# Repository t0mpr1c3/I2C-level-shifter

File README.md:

I2C-level-shifter
=================

I2C voltage level converter with LDO voltage regulator.

Following NXP application note AN10441.

Released under the [Creative Commons License Attribution-ShareAlike 3.0](http://creativecommons.org/licenses/by-sa/3.0/)

Version history
---------------

_IL01_

First version.

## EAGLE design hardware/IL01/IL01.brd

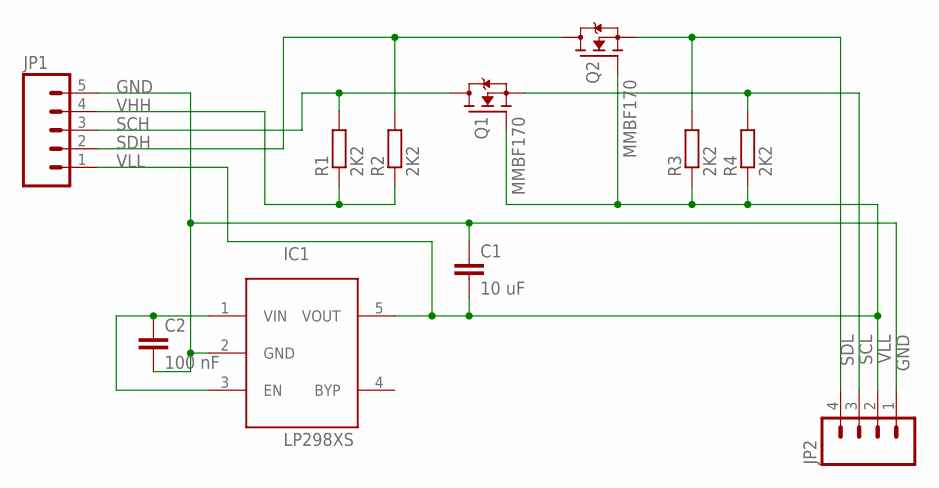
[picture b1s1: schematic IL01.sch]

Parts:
C1: 10 uF; C1206
C2: 100 nF; C0805
IC1: LP298XS; SOT23-5L
JP1: M05PTH; 1X05
JP2: M04PTH; 1X04
Q1, Q2: MMBF170; SOT-23
R1, R2, R3, R4: 2K2; R0603

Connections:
GND: C1.1, C2.2, IC1.2 (GND), JP1.5, JP2.1
SCH: JP1.3, Q1.3 (D), R1.2
SCL: JP2.4, Q2.2 (S), R3.2
SDH: JP1.2, Q2.3 (D), R2.2
SDL: JP2.3, Q1.2 (S), R4.2
VHH: C2.1, IC1.1 (VIN), IC1.3 (EN), JP1.4, R1.1, R2.1
VLL: C1.2, IC1.5 (VOUT), JP1.1, JP2.2, Q1.1 (G), Q2.1 (G), R3.1, R4.1

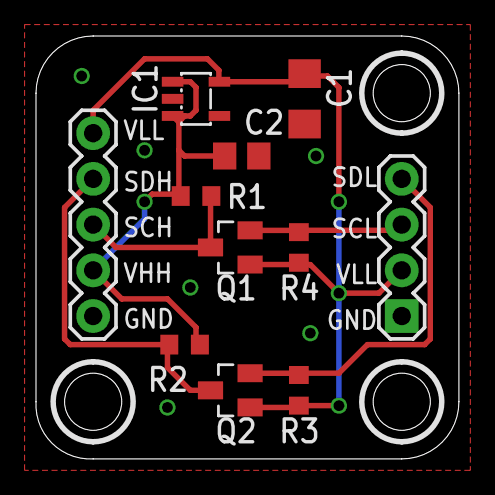
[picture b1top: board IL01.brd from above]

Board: 4 copper layers, 23.5 x 23.5 mm, 12 parts (1 on the bottom side), 7 nets.

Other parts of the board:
U$3: OSHW-LOGO-S

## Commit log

2013-11-18 reversed headers
2013-11-26 tweak gerbers
2013-12-03 IL01 for Seeedstudio
2013-12-24 IL01 Elecrow order

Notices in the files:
hardware/IL01/IL01.brd:
CC BY-SA 3.0
parts and their libraries:
SparkFun: Licensing: CC v3.0 Share-Alike You are welcome to use this library for commercial purposes.
